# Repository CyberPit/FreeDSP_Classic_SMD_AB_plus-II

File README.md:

# FreeDSP_Classic_SMD_AB_plus-II

- 2in6out RCA jacks
- Integrated FreeUSBi
- A/B Selectable EEPROMs
- PCM5102A for DIG6/7
- ADAU1701 Board with selectable A/B Boot
- 0805(2.0mm x 1.25mm) SMD Resistors & Capacitors
- Through-Hole Ele-Caps
- Unity Gain Analog Audio I/O
- Absolute Phase transparent.
- Power ON/OFF/Reset Audio Pops Mute
- Buffered I2S I/O Headers (with Enable control feature)
- I6S Header pin for external DACs. 

Project web page: (Direct Link)
https://cyberpithilo.web.fc2.com/audio/freedsp/index.html

Project web page: (Yandex Machine Translation)
https://translate.yandex.com/translate?url=https%3A%2F%2Fcyberpithilo.web.fc2.com%2Faudio%2Ffreedsp%2Findex.html&lang=ja-en

Project web page: (Google Machine Translation)
https://translate.google.com/translate?hl=ja&sl=ja&tl=en&u=https%3A%2F%2Fcyberpithilo.web.fc2.com%2Faudio%2Ffreedsp%2Findex.html

I had the ver0.1 board ordered to JLPCB (https://jlcpcb.com/) 
You can order SMT and Boards. My ordered PCBA file package is also included. 

# License
This work and all other materials under https://github.com/freeDSP are licensed under a Creative Commons Attribution Share-Alike 4.0 license. This allows for both personal and commercial derivative works, as long as they credit freeDSP and release their designs under the same license.

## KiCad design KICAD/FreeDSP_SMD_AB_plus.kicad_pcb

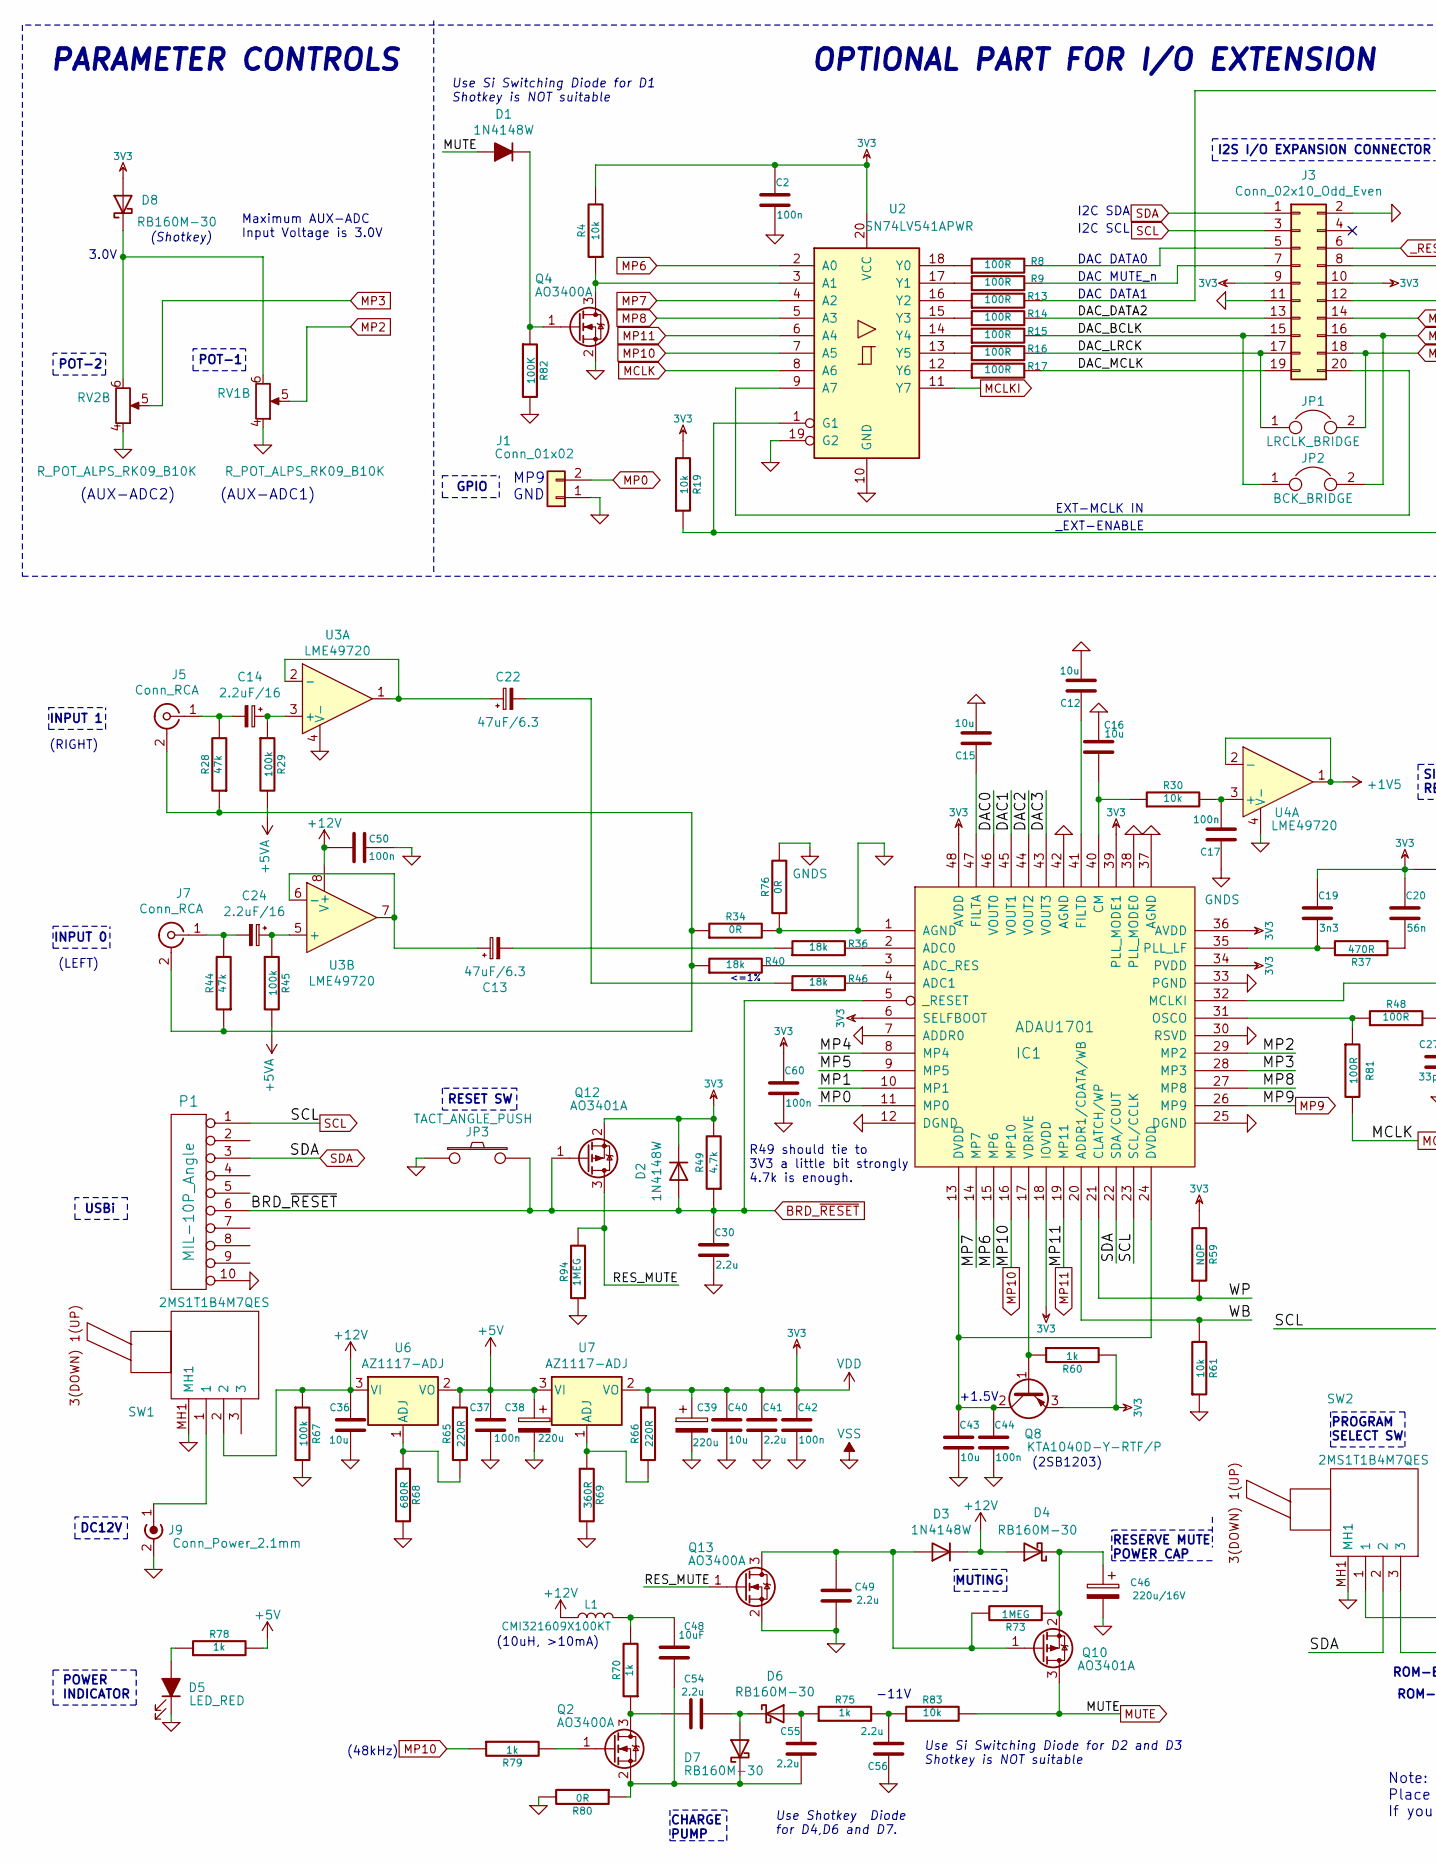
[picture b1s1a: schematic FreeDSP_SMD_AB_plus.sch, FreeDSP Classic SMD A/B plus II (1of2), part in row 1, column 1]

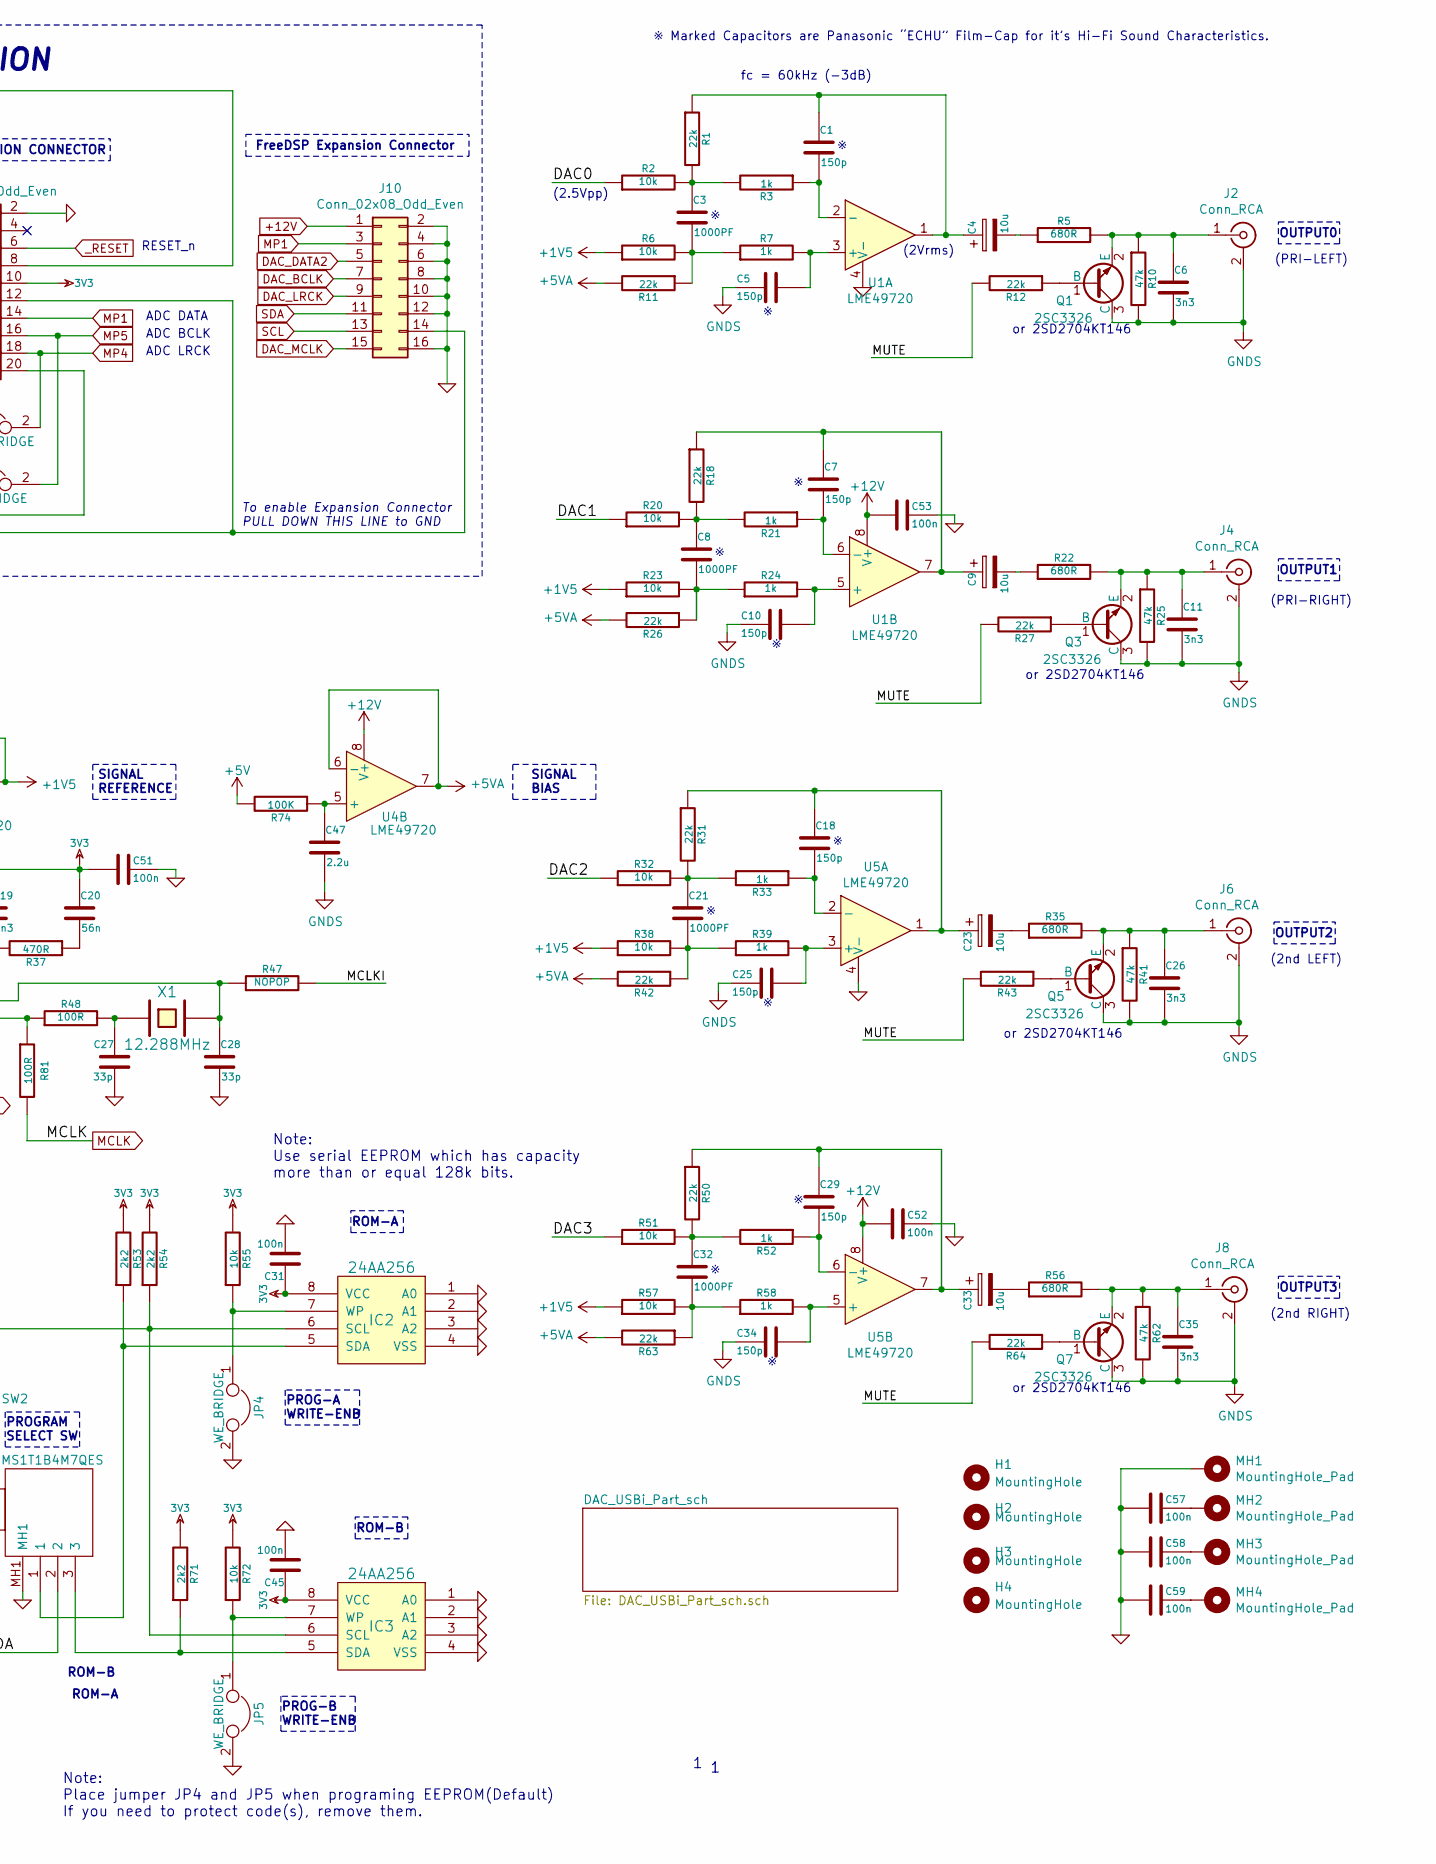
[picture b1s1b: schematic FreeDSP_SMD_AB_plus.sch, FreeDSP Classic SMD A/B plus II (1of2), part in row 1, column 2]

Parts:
C1, C5, C7, C10, C18, C25, C29, C34: 150p; C_0805_HandSoldering
C2, C17, C31, C37, C42, C44, C45, C50, C51, C52, C53, C57, C58, C59, C60: 100n; C_0805_HandSoldering
C3, C8, C21, C32: 1000PF; C_0805_HandSoldering
C4, C9, C23, C33: 10u; CP_Radial_D5.0mm_P2.00mm
C6, C11, C19, C26, C35: 3n3; C_0805_HandSoldering
C12, C15, C16, C36, C40, C43: 10u; C_0805_HandSoldering
C13, C22: 47uF/6.3; CP_Radial_D4.0mm_P2.00mm
C14, C24: 2.2uF/16; CP_Radial_D4.0mm_P2.00mm
C20: 56n; C_0805_HandSoldering
C27, C28: 33p; C_0805_HandSoldering
C30, C41, C47, C49, C54, C55, C56: 2.2u; C_0805_HandSoldering
C38, C39: 220u; CP_Radial_D8.0mm_P5.00mm
C46: 220u/16V; CP_Radial_D10.0mm_P5.00mm
C48: 10uF; C_1206_HandSoldering
D1, D2, D3: 1N4148W; D_SOD-123
D4, D6, D7, D8: RB160M-30; D_SOD-123
D5: LED_RED; LED_0603_HandSoldering
H1, H2, H3, H4: MountingHole; MountingHole_2.7mm_M2.5
IC1: ADAU1701; LQFP-48_7x7mm_Pitch0.5mm
IC2, IC3: 24AA256; SOIC-8_3.9x4.9mm_Pitch1.27mm
J1: Conn_01x02; PinHeader_1x02_P2.54mm_Vertical
J2, J4, J5, J6, J7, J8: Conn_RCA; RJ-2410N
J3: Conn_02x10_Odd_Even; IDC-Header_2x10_P2.54mm_Vertical
J9: Conn_Power_2.1mm; BARREL_JACK
J10: Conn_02x08_Odd_Even; Pin_Header_Straight_2x08_Pitch2.54mm
JP1: LRCLK_BRIDGE; Pin_Header_Straight_1x02_Pitch2.54mm
JP2: BCK_BRIDGE; Pin_Header_Straight_1x02_Pitch2.54mm
JP3: TACT_ANGLE_PUSH; SW_Tactile_SPST_Angled_PTS645Vx83-2LFS
JP4, JP5: WE_BRIDGE; Pin_Header_Straight_1x02_Pitch2.54mm
L1: CMI321609X100KT; Inductor_1212; MPN LQH2MCN100K02L
MH1: MountingHole_Pad; MountingHole_3.2mm_M3_Pad_Via
MH2, MH3, MH4: MountingHole_Pad; MountingHole_3.2mm_M3_Pad
P1: MIL-10P_Angle; IDC-Header_2x05_P2.54mm_Horizontal
Q1, Q3, Q5, Q7: 2SC3326; SOT-23
Q2, Q4, Q13: AO3400A; SOT-23
Q8: KTA1040D-Y-RTF/P; TO-252-2
Q10, Q12: AO3401A; SOT-23
R1, R11, R12, R18, R26, R27, R31, R42, R43, R50, R63, R64: 22k; R_0805_HandSoldering
R2, R4, R6, R19, R20, R23, R30, R32, R38, R51, R55, R57, R61, R72, R83: 10k; R_0805_HandSoldering
R3, R7, R21, R24, R33, R39, R52, R58, R60, R70, R75, R78, R79: 1k; R_0805_HandSoldering
R5, R22, R35, R56, R68: 680R; R_0805_HandSoldering
R8, R9, R13, R14, R15, R16, R17, R48, R81: 100R; R_0805_HandSoldering
R10, R25, R28, R41, R44, R62: 47k; R_0805_HandSoldering
R29, R45, R67: 100k; R_0805_HandSoldering
R34, R76, R80: 0R; R_0805_HandSoldering
R36, R40, R46: 18k; R_0805_HandSoldering
R37: 470R; R_0805_HandSoldering
R47: NOPOP; R_0805_HandSoldering
R49: 4.7k; R_0805_HandSoldering
R53, R54, R71: 2k2; R_0805_HandSoldering
R59: NOP; R_0805_HandSoldering
R65, R66: 220R; R_0805_HandSoldering
R69: 360R; R_0805_HandSoldering
R73, R94: 1MEG; R_0805_HandSoldering
R74, R82: 100K; R_0805_HandSoldering
RV1, RV2: R_POT_ALPS_RK09_B10K; Potentiometer_Alps_RK09L_Double_Vertical
SW1, SW2: 2MS1T1B4M7QES; Manufacturer_Part_Number 2MS1T1B4M7QES
U1, U3, U4, U5: LME49720; SOIC127P600X175-8N
U2: SN74LV541APWR; TSSOP-20_W4.4mm
U6, U7: AZ1117-ADJ; SOT-223-3_TabPin2
X1: 12.288MHz; Crystal_HC49-U_Vertical

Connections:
3V3: C2.1, C19.1, C20.1, C31.1, C39.1, C40.1, C41.1, C42.1, C45.1, C51.2, C60.1, D2.1 (K), D8.2 (A), IC1.6 (SELFBOOT), IC1.18 (IOVDD), IC1.34 (PVDD), IC1.36 (AVDD), IC1.39 (PLL_MODE1), IC1.48 (AVDD), IC2.8 (VCC), IC3.8 (VCC), J3.9, J3.10, Q8.3 (E), Q12.2 (S), R4.2, R19.2, R49.2, R53.2, R54.2, R55.2, R59.2, R60.2, R66.1, R71.2, R72.2, U2.20 (VCC), U7.2 (VO); also elsewhere on the board
+1V5: R6.1, R23.1, R38.1, R57.1, U4.1, U4.2 (-)
+5V: C37.1, C38.1, R65.1, R74.2, R78.2, U6.2 (VO), U7.3 (VI)
+5VA: R11.2, R26.2, R29.2, R42.2, R45.2, R63.2, U4.6 (-), U4.7
+12V: C36.1, C50.2, C52.2, C53.2, D3.1 (K), D4.2 (A), J10.1, L1.1, R67.1, SW1.2, U1.8 (V+), U3.8 (V+), U4.8 (V+), U5.8 (V+), U6.3 (VI)
/DAC0: IC1.46 (VOUT0), R2.1
/DAC1: IC1.45 (VOUT1), R20.1
/DAC2: IC1.44 (VOUT2), R32.1
/DAC3: IC1.43 (VOUT3), R51.1
/RES_MUTE: Q12.3 (D), Q13.1 (G), R94.2
/WB: IC1.20 (ADDR1/CDATA/WB), R61.2
/WP: IC1.21 (CLATCH/WP), R59.1
BRD_~RESET: C30.1, D2.2 (A), IC1.5 (_RESET), JP3.2, P1.6, Q12.1 (G), R49.1; also elsewhere on the board
DAC_BCLK: J3.15, J10.7, JP2.1, R15.2
DAC_DATA2: J3.13, J10.5, R14.2
DAC_LRCK: J3.17, J10.9, JP1.1, R16.2
DAC_MCLK: J3.19, J10.15, R17.2
GND: C2.2, C12.2, C15.2, C16.2, C27.2, C28.2, C30.2, C31.2, C36.2, C37.2, C38.2, C39.2, C40.2, C41.2, C42.2, C43.2, C44.2, C45.2, C46.2, C49.2, C50.1, C51.1, C52.1, C53.1, C56.1, C57.2, C58.2, C59.2, C60.2, D5.1 (K), IC1.1 (AGND), IC1.7 (ADDR0), IC1.12 (DGND), IC1.25 (DGND), IC1.30 (RSVD), IC1.33 (PGND), IC1.37 (AGND), IC1.38 (PLL_MODE0), IC1.42 (AGND), IC2.1 (A0), IC2.2 (A1), IC2.3 (A2), IC2.4 (VSS), IC3.1 (A0), IC3.2 (A1), IC3.3 (A2), IC3.4 (VSS), J1.1, J3.2, J3.11, J9.2 (Ext), J10.2, J10.4, J10.6, J10.8, J10.10, J10.12, J10.16, JP3.1, JP4.2, JP5.2, MH1.1, P1.10, Q4.2 (S), Q13.2 (S), R34.2, R61.1, R67.2, R68.2, R69.2, R76.1, R80.2, R82.2, R94.1, RV1.4, RV2.4, SW1.MH1, SW2.MH1, U1.4 (V-), U2.10 (GND), U2.19 (G2), U3.4 (V-), U4.4 (V-), U5.4 (V-); also elsewhere on the board
GNDS: C5.2, C6.2, C10.2, C11.2, C17.1, C25.2, C26.2, C34.2, C35.2, C47.2, J2.2 (Ext), J4.2 (Ext), J6.2 (Ext), J8.2 (Ext), Q1.3 (C), Q3.3 (C), Q5.3 (C), Q7.3 (C), R10.2, R25.2, R41.2, R62.2, R76.2; also elsewhere on the board
MCLK: R81.2, U2.8 (A6)
MCLKI: R47.2, U2.11 (Y7)
MP0: IC1.11 (MP0), J1.2
MP1: IC1.10 (MP1), J3.14, J10.3
MP2: IC1.29 (MP2), RV1.5
MP3: IC1.28 (MP3), RV2.5
MP4: IC1.8 (MP4), J3.18, JP1.2
MP5: IC1.9 (MP5), J3.16, JP2.2
MP6: IC1.15 (MP6), U2.2 (A0)
MP7: IC1.14 (MP7), U2.4 (A2)
MP8: IC1.27 (MP8), U2.5 (A3)
MP9: IC1.26 (MP9); also elsewhere on the board
MP10: IC1.16 (MP10), R79.1, U2.7 (A5); also elsewhere on the board
MP11: IC1.19 (MP11), U2.6 (A4); also elsewhere on the board
MUTE: D1.2 (A), Q10.3 (D), R12.2, R27.2, R43.2, R64.2, R83.2; also elsewhere on the board
unnamed: C1.1, C4.1, R1.1, U1.1
unnamed: C1.2, R3.1, U1.2 (-)
unnamed: C3.1, R1.2, R2.2, R3.2
unnamed: C3.2, R6.2, R7.1, R11.1
unnamed: C4.2, R5.1
unnamed: C5.1, R7.2, U1.3 (+)
unnamed: C6.1, J2.1 (In), Q1.2 (E), R5.2, R10.1
unnamed: C7.1, C9.1, R18.1, U1.7
unnamed: C7.2, R21.1, U1.6 (-)
unnamed: C8.1, R18.2, R20.2, R21.2
unnamed: C8.2, R23.2, R24.1, R26.1
unnamed: C9.2, R22.1
unnamed: C10.1, R24.2, U1.5 (+)
unnamed: C11.1, J4.1 (In), Q3.2 (E), R22.2, R25.1
unnamed: C12.1, IC1.41 (FILTD)
unnamed: C13.1, U3.6 (-), U3.7
unnamed: C13.2, R36.1
unnamed: C14.1, R29.1, U3.3 (+)
unnamed: C14.2, J5.1 (In), R28.2
unnamed: C15.1, IC1.47 (FILTA)
unnamed: C16.1, IC1.40 (CM), R30.1
unnamed: C17.2, R30.2, U4.3 (+)
unnamed: C18.1, C23.1, R31.1, U5.1
unnamed: C18.2, R33.1, U5.2 (-)
unnamed: C19.2, IC1.35 (PLL_LF), R37.2
unnamed: C20.2, R37.1
unnamed: C21.1, R31.2, R32.2, R33.2
unnamed: C21.2, R38.2, R39.1, R42.1
unnamed: C22.1, U3.1, U3.2 (-)
unnamed: C22.2, R46.1
unnamed: C23.2, R35.1
unnamed: C24.1, R45.1, U3.5 (+)
unnamed: C24.2, J7.1 (In), R44.2
unnamed: C25.1, R39.2, U5.3 (+)
unnamed: C26.1, J6.1 (In), Q5.2 (E), R35.2, R41.1
unnamed: C27.1, R48.2, X1.1
unnamed: C28.1, IC1.32 (MCLKI), R47.1, X1.2
unnamed: C29.1, C33.1, R50.1, U5.7
unnamed: C29.2, R52.1, U5.6 (-)
unnamed: C32.1, R50.2, R51.2, R52.2
unnamed: C32.2, R57.2, R58.1, R63.1
unnamed: C33.2, R56.1
unnamed: C34.1, R58.2, U5.5 (+)
unnamed: C35.1, J8.1 (In), Q7.2 (E), R56.2, R62.1
unnamed: C43.1, C44.1, IC1.13 (DVDD), IC1.24 (DVDD), Q8.2 (C)
unnamed: C46.1, D4.1 (K), Q10.2 (S), R73.1
unnamed: C47.1, R74.1, U4.5 (+)
unnamed: C48.1, L1.2, R70.2
unnamed: C48.2, C55.2, D7.1 (K), Q2.2 (S), R80.1
unnamed: C49.1, D3.2 (A), Q10.1 (G), Q13.3 (D), R73.2
unnamed: C54.1, Q2.3 (D), R70.1
unnamed: C54.2, D6.1 (K), D7.2 (A)
unnamed: C55.1, D6.2 (A), R75.1
unnamed: C56.2, R75.2, R83.1
unnamed: C57.1, MH2.1
unnamed: C58.1, MH3.1
unnamed: C59.1, MH4.1
unnamed: D1.1 (K), Q4.1 (G), R82.1
unnamed: D5.2 (A), R78.1
unnamed: D8.1 (K), RV1.6, RV2.6
unnamed: IC1.2 (ADC0), R36.2
unnamed: IC1.3 (ADC_RES), R40.2
unnamed: IC1.4 (ADC1), R46.2
unnamed: IC1.17 (VDRIVE), Q8.1 (B), R60.1
unnamed: IC1.31 (OSCO), R48.1, R81.1
unnamed: IC2.5 (SDA), R53.1, SW2.1
unnamed: IC2.7 (WP), JP4.1, R55.1
unnamed: IC3.5 (SDA), R71.1, SW2.3
unnamed: IC3.7 (WP), JP5.1, R72.1
unnamed: J3.5, R8.2
unnamed: J3.7, R9.2
unnamed: J3.8, R13.2
unnamed: J3.20, U2.9 (A7)
unnamed: J5.2 (Ext), J7.2 (Ext), R28.1, R34.1, R40.1, R44.1
unnamed: J9.1 (In), SW1.1
unnamed: J3.12, J10.14, R19.1, U2.1 (G1)
unnamed: Q1.1 (B), R12.1
unnamed: Q2.1 (G), R79.2
unnamed: Q3.1 (B), R27.1
unnamed: Q4.3 (D), R4.1, U2.3 (A1)
unnamed: Q5.1 (B), R43.1
unnamed: Q7.1 (B), R64.1
unnamed: R8.1, U2.18 (Y0)
unnamed: R9.1, U2.17 (Y1)
unnamed: R13.1, U2.16 (Y2)
unnamed: R14.1, U2.15 (Y3)
unnamed: R15.1, U2.14 (Y4)
unnamed: R16.1, U2.13 (Y5)
unnamed: R17.1, U2.12 (Y6)
unnamed: R65.2, R68.1, U6.1 (ADJ)
unnamed: R66.2, R69.1, U7.1 (ADJ)
SCL: IC1.23 (SCL/CCLK), IC2.6 (SCL), IC3.6 (SCL), J3.3, J10.13, P1.1, R54.1; also elsewhere on the board
SDA: IC1.22 (SDA/COUT), J3.1, J10.11, P1.3, SW2.2; also elsewhere on the board

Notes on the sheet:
<=1%
RESET SW
DAC DATA0
DAC MUTE_n
I2C SCL
I2C SDA
RESET_n
DAC DATA1
EXT-MCLK IN
ADC LRCK
ADC BCLK
ADC DATA
I2S I/O EXPANSION CONNECTOR
POT-1
POT-2
ROM-A
ROM-B
USBi
DC12V
fc = 60kHz (-3dB)
(2.5Vpp)
(2Vrms)
MUTING
INPUT 0
INPUT 1
OUTPUT0
OUTPUT1
OUTPUT2
OUTPUT3
PROGRAM SELECT SW
SIGNAL REFERENCE
SIGNAL BIAS
_EXT-ENABLE
PROG-A WRITE-ENB
PROG-B WRITE-ENB
GPIO
MP9 GND
OPTIONAL PART FOR I/O EXTENSION
FreeDSP Expansion Connector
Note: Use serial EEPROM which has capacity more than or equal 128k bits.

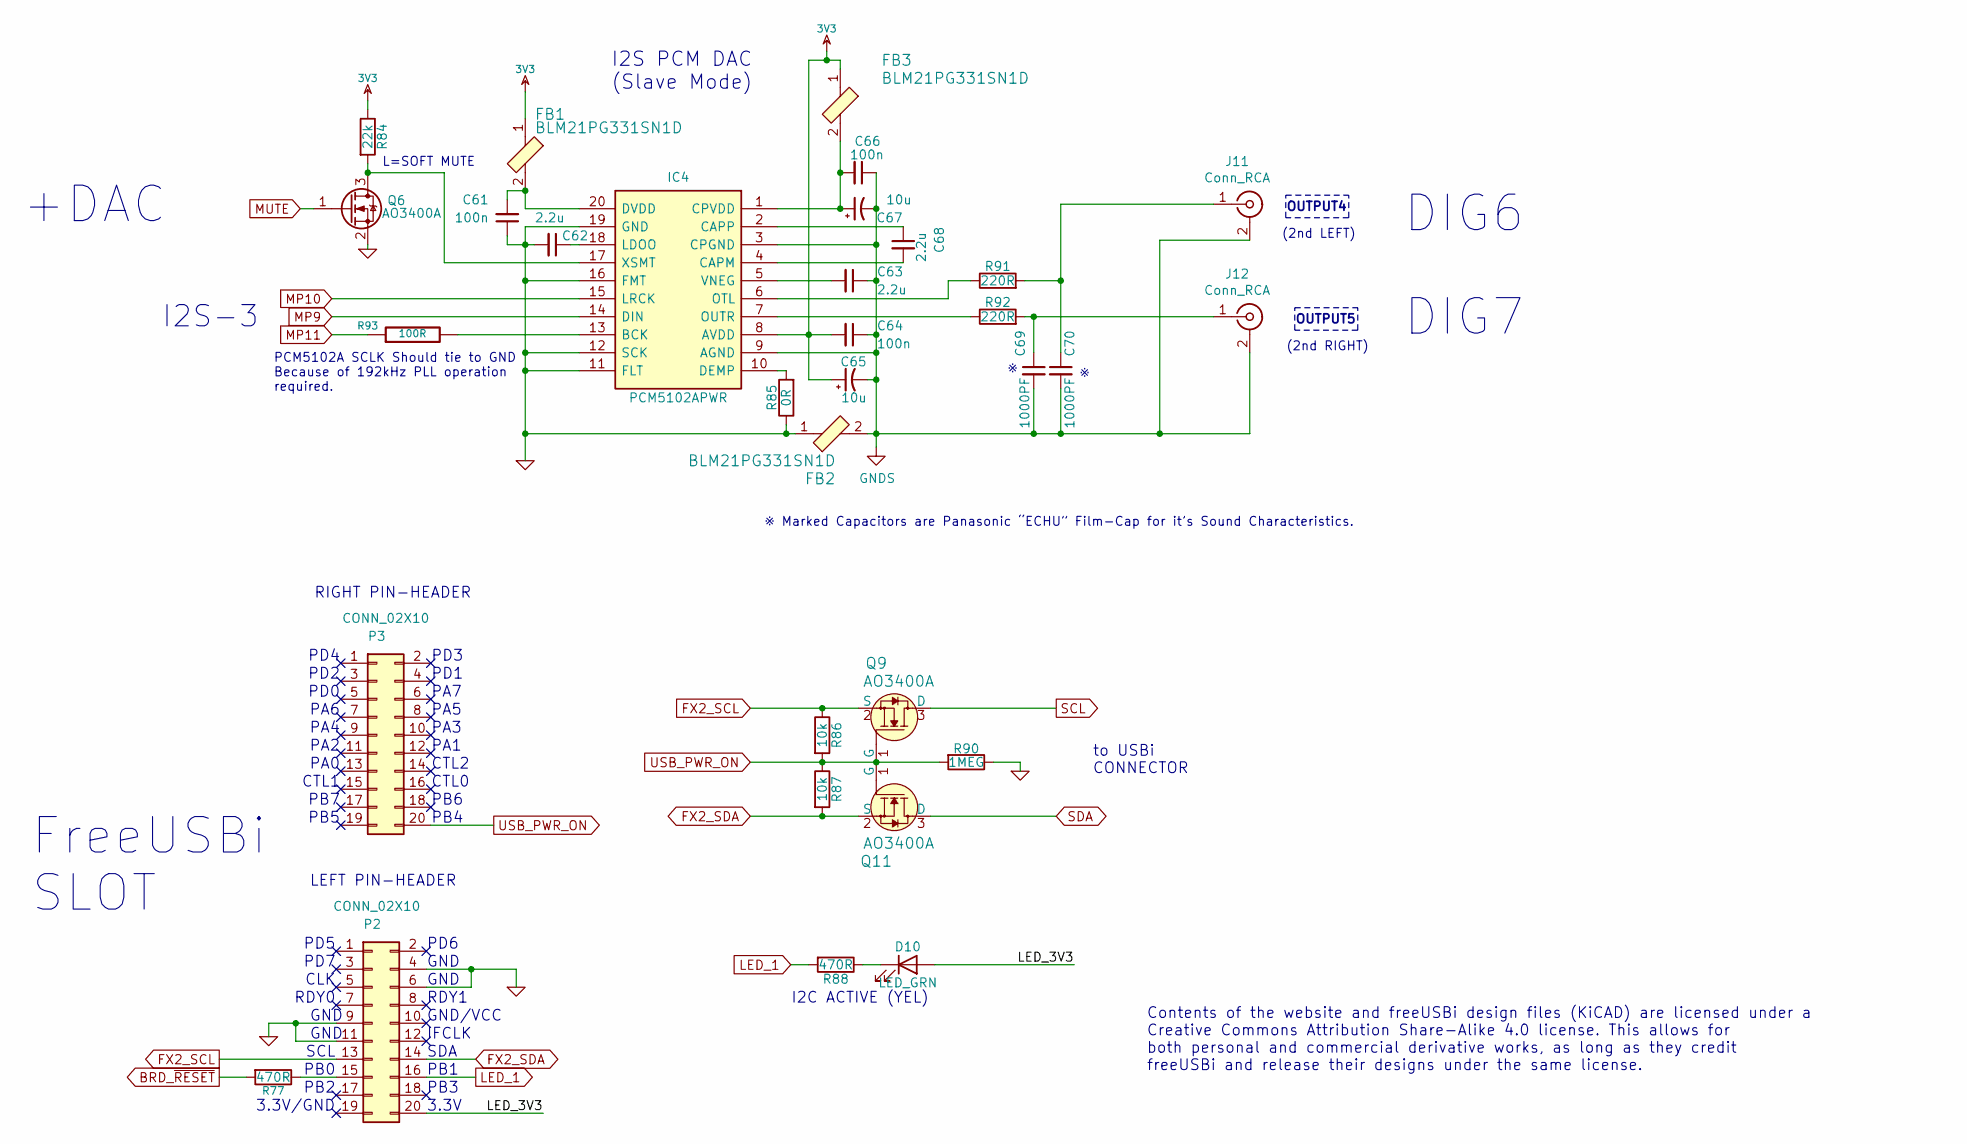
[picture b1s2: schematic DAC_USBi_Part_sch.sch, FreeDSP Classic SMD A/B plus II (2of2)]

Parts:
C61, C64, C66: 100n; C_0805_HandSoldering
C62, C63, C68: 2.2u; C_0805_HandSoldering
C65, C67: 10u; C_0805_HandSoldering
C69, C70: 1000PF; C_0805_HandSoldering
D10: LED_GRN; LED_0603_HandSoldering
FB1, FB2, FB3: BLM21PG331SN1D; 0805; MPN BLM21PG331SN1D; Digi-Key_PN 490-5988-1-ND
IC4: PCM5102APWR; TSSOP-20_4.4x6.5mm_P0.65mm; Manufacturer_Part_Number PCM5102APWR
J11, J12: Conn_RCA; RJ-2410N
P2, P3: CONN_02X10; PinSocket_2x10_P2.54mm_Vertical
Q6: AO3400A; SOT-23
Q9, Q11: AO3400A; SOT-23-3; MPN 2N7002; Digi-Key_PN 2N7002NCT-ND
R77, R88: 470R; R_0805_HandSoldering
R84: 22k; R_0805_HandSoldering
R85: 0R; R_0805_HandSoldering
R86, R87: 10k; R_0805_HandSoldering
R90: 1MEG; R_0805_HandSoldering
R91, R92: 220R; R_0805_HandSoldering
R93: 100R; R_0805_HandSoldering

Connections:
3V3: C64.2, C65.1, FB1.1, FB3.1, IC4.8 (AVDD), R84.1; also elsewhere on the board
/DAC_USBi_Part_sch/LED_3V3: D10.2 (A), P2.20
BRD_~RESET: R77.2; also elsewhere on the board
FX2_SCL: P2.13, Q9.2 (S), R86.1
FX2_SDA: P2.14, Q11.2 (S), R87.2
GND: C61.1, C62.2, FB2.1, IC4.11 (FLT), IC4.12 (SCK), IC4.16 (FMT), IC4.19 (GND), P2.4, P2.6, P2.9, P2.11, Q6.2 (S), R85.1, R90.1; also elsewhere on the board
GNDS: C63.1, C64.1, C65.2, C66.1, C67.2, C69.2, C70.2, FB2.2, IC4.3 (CPGND), IC4.9 (AGND), J11.2 (Ext), J12.2 (Ext); also elsewhere on the board
LED_1: P2.16, R88.2
MP9: IC4.14 (DIN); also elsewhere on the board
MP10: IC4.15 (LRCK); also elsewhere on the board
MP11: R93.1; also elsewhere on the board
MUTE: Q6.1 (G); also elsewhere on the board
unnamed: C61.2, FB1.2, IC4.20 (DVDD)
unnamed: C62.1, IC4.18 (LDOO)
unnamed: C63.2, IC4.5 (VNEG)
unnamed: C66.2, C67.1, FB3.2, IC4.1 (CPVDD)
unnamed: C68.1, IC4.2 (CAPP)
unnamed: C68.2, IC4.4 (CAPM)
unnamed: C69.1, J12.1 (In), R92.2
unnamed: C70.1, J11.1 (In), R91.2
unnamed: D10.1 (K), R88.1
unnamed: IC4.6 (OTL), R91.1
unnamed: IC4.7 (OUTR), R92.1
unnamed: IC4.10 (DEMP), R85.2
unnamed: IC4.13 (BCK), R93.2
unnamed: IC4.17 (XSMT), Q6.3 (D), R84.2
unnamed: P2.15, R77.1
SCL: Q9.3 (D); also elsewhere on the board
SDA: Q11.3 (D); also elsewhere on the board
USB_PWR_ON: P3.20, Q9.1 (G), Q11.1 (G), R86.2, R87.1, R90.2

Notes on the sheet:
I2S PCM DAC (Slave Mode)
I2S-3
DIG6
L=SOFT MUTE
PD6
RDY1
IFCLK
SDA
PB1
PB3
PB0
PB2
SCL
RDY0
CLK
PD7
PD5
GND
GND/VCC
PD3
PD1
PA7
PA5
PA3
PA1
PA2
PA4
PA6
PA0
PD0
PD2
PD4
CTL1
CTL0
CTL2
PB6
PB4
PB7
PB5
3.3V/GND

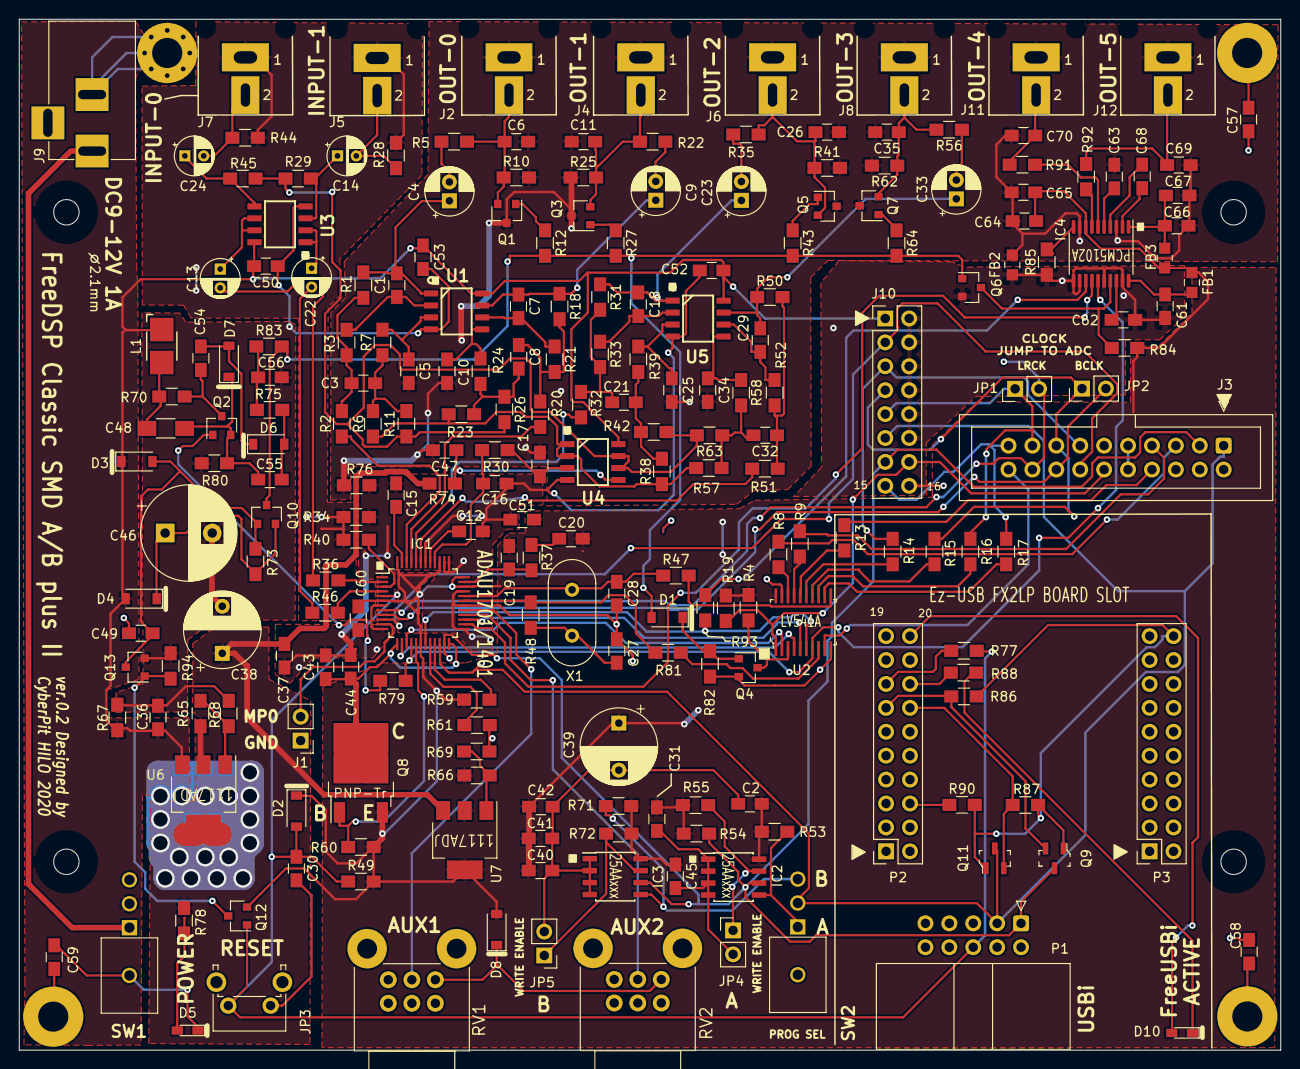
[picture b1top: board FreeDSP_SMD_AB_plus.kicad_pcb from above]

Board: 2 copper layers, 134.0 x 109.5 mm, 233 parts (0 on the bottom side), 147 nets.

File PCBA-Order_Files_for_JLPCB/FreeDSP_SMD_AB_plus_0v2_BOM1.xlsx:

Comment | Designator | Footprint | JLCPCB Part #（optional）
150p | C1,C5,C7,C10,C25,C29,C34,C18 | C_0805_HandSoldering | C1716
10u | C12,C36,C40,C43,C15,C16,C65,C67 | C_0805_HandSoldering | C15850
100n | C2,C31,C37,C42,C44,C45,C17,C50,C51,C52,C53,C57,C58,C59,C60,C61,C64,C66 | C_0805_HandSoldering | C49678
56n | C20 | C_0805_HandSoldering | C1756
33p | C27,C28 | C_0805_HandSoldering | C1814
1000PF | C3,C8,C32,C21,C69,C70 | C_0805_HandSoldering | C46653
2.2u | C30,C41,C47,C49,C54,C55,C56,C62,C63,C68 | C_0805_HandSoldering | C49217
10uF | C48 | C_1206_HandSoldering | C13585
3n3 | C6,C11,C26,C35,C19 | C_0805_HandSoldering | C53175
LED_GRN | D10 | LED_0603_HandSoldering | C72043
1N4148W | D3,D1,D2 | D_SOD-123 | C81598
LED_RED | D5 | LED_0603_HandSoldering | C2286
B5819W | D6,D7,D4,D8 | D_SOD-123 | C8598
GZ2012D601TF | FB1,FB2,FB3 | 0805 | C1017
ADAU1701 | IC1 | LQFP-48_7x7mm_Pitch0.5mm | C389590
24AA256 | IC3,IC2 | SOIC-8_3.9x4.9mm_Pitch1.27mm | C6482
PCM5102APWR | IC4 | TSSOP-20_4.4x6.5mm_P0.65mm | C107671
CMI321609X100KT | L1 | Inductor_1206 | C1051
2SC3326 | Q1,Q3,Q7,Q5 | SOT-23 | C27829
AO3401A | Q10,Q12 | SOT-23-3L | C15127
2N7002 | Q2,Q4,Q6,Q13,Q9,Q11 | SOT-23-3 | C8545
KTA1040D-Y-RTF/P | Q8 | TO-252-2 | C69791
22k | R1,R11,R12,R18,R26,R27,R31,R42,R43,R50,R63,R64,R84 | R_0805_HandSoldering | C17560
47k | R10,R25,R28,R41,R44,R62 | R_0805_HandSoldering | C17713
4.7k | R49 | R_0805_HandSoldering | C23162
10k | R2,R6,R19,R20,R23,R30,R32,R38,R51,R55,R57,R61,R72,R4,R83,R86,R87 | R_0805_HandSoldering | C17414
100k | R29,R45,R67 | R_0805_HandSoldering | C17407
0R | R34,R68,R69,R76,R80,R85 | R_0805_HandSoldering | C17477
18k | R36,R40,R46 | R_0805_HandSoldering | C17506
470R | R37,R77,R88 | R_0805_HandSoldering | C17710
680R | R5,R22,R35,R56 | R_0805_HandSoldering | C17798
2k2 | R53,R54,R71 | R_0805_HandSoldering | C17520
1k | R70,R3,R7,R21,R24,R33,R39,R52,R58,R60,R75,R78,R79 | R_0805_HandSoldering | C17513
1MEG | R73,R90,R94 | R_0805_HandSoldering | C17514
100K | R74,R82 | R_0805_HandSoldering | C17407
100R | R8,R9,R13,R14,R15,R16,R17,R48,R81,R93 | R_0805_HandSoldering | C17408
220R | R91,R92 | R_0805_HandSoldering | C17557
OPA1652 | U1,U3,U4,U5 | SOIC127P600X175-8N | C30025
SN74LV541APWR | U2 | TSSOP-20_4.4x6.5x0.65P | C406870
AMS1117-5.0 | U6 | SOT-223 | C6187
AMS1117-3.3 | U7 | SOT-223 | C6186

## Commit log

2020-10-11 FreeDSP Classic SMD A/B plus II ver.2 Ki-CAD Files
2020-10-11 Version 0.2 Board Gerber Files
2020-10-11 Actual Photsos are ver.1 Board.
2020-10-11 PCBA Oder Package for JLPCB (https://jlcpcb.com/)
2020-10-11 An extended version of FreeDSP Classic SMD A/B
2020-10-16 R49 was changed to 4K7
2020-10-16 Ver.2 PDF files added
2021-01-06 Casing Photo
2021-02-23 RightMark Audio Analyzer Test Report HTML Format
    https://audio.rightmark.org/index_new.shtml
2021-02-23 Board Casing Images
2021-03-13 Application Examples / 3way Crossover
2021-03-13 Application Examples
2021-03-13 Sample Application 3way Crossover fs=96kHz
2021-03-13 Application Example
2021-03-13 ScreenShots
2021-03-13 RightMark Audio Analyzer Test Report
2021-12-09 Fixed format of BOM and CPL
2021-12-11 Fixed format error and CPL infomation
    FB1, FB2, FB3, U2 are SMD parts.
2023-07-13 Fixed PCBA Package for JLPCB (https://jlcpcb.com/)
2024-04-08 Variable 2way Crossover Frequency Channel Divider
2024-04-08 Variable Crossover Frequency 2way Channel Divider

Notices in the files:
KICAD/DAC_USBi_Part_sch.sch:
Contents of the website and freeUSBi design files (KiCAD) are licensed under a
freeUSBi and release their designs under the same license.
